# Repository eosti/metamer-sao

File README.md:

# Metamer SAO
A collection of files related to the [Metamer SAO](https://reidsoxharris.me/metamer-sao)

v2 of the badge (first seen at Hackaday 2024) can be found in the `v2_altium` directory, though it's just boardfiles and schematic PDFs. 
Because reasons I had to port it into KiCAD for v2.1, which can be found in the `v2.1_kicad` directory along with all generated gerbers and PnP files required for assembly. 
The `generators` directory has some code for auto-generating C data structures for normalizing brightness. 

Some MicroPython code that you can run on the badge is found in the `micropython` directory. 
The code used on the PY32F002B MCU used to bootstrap I2C is in the `py32` directory, and current builds are in `py32/releases`.

The code I used to generate the graphs for my talk, [Beyond RGB](https://reidsoxharris.me/beyondrgb/) can be found in `python_graphs`.

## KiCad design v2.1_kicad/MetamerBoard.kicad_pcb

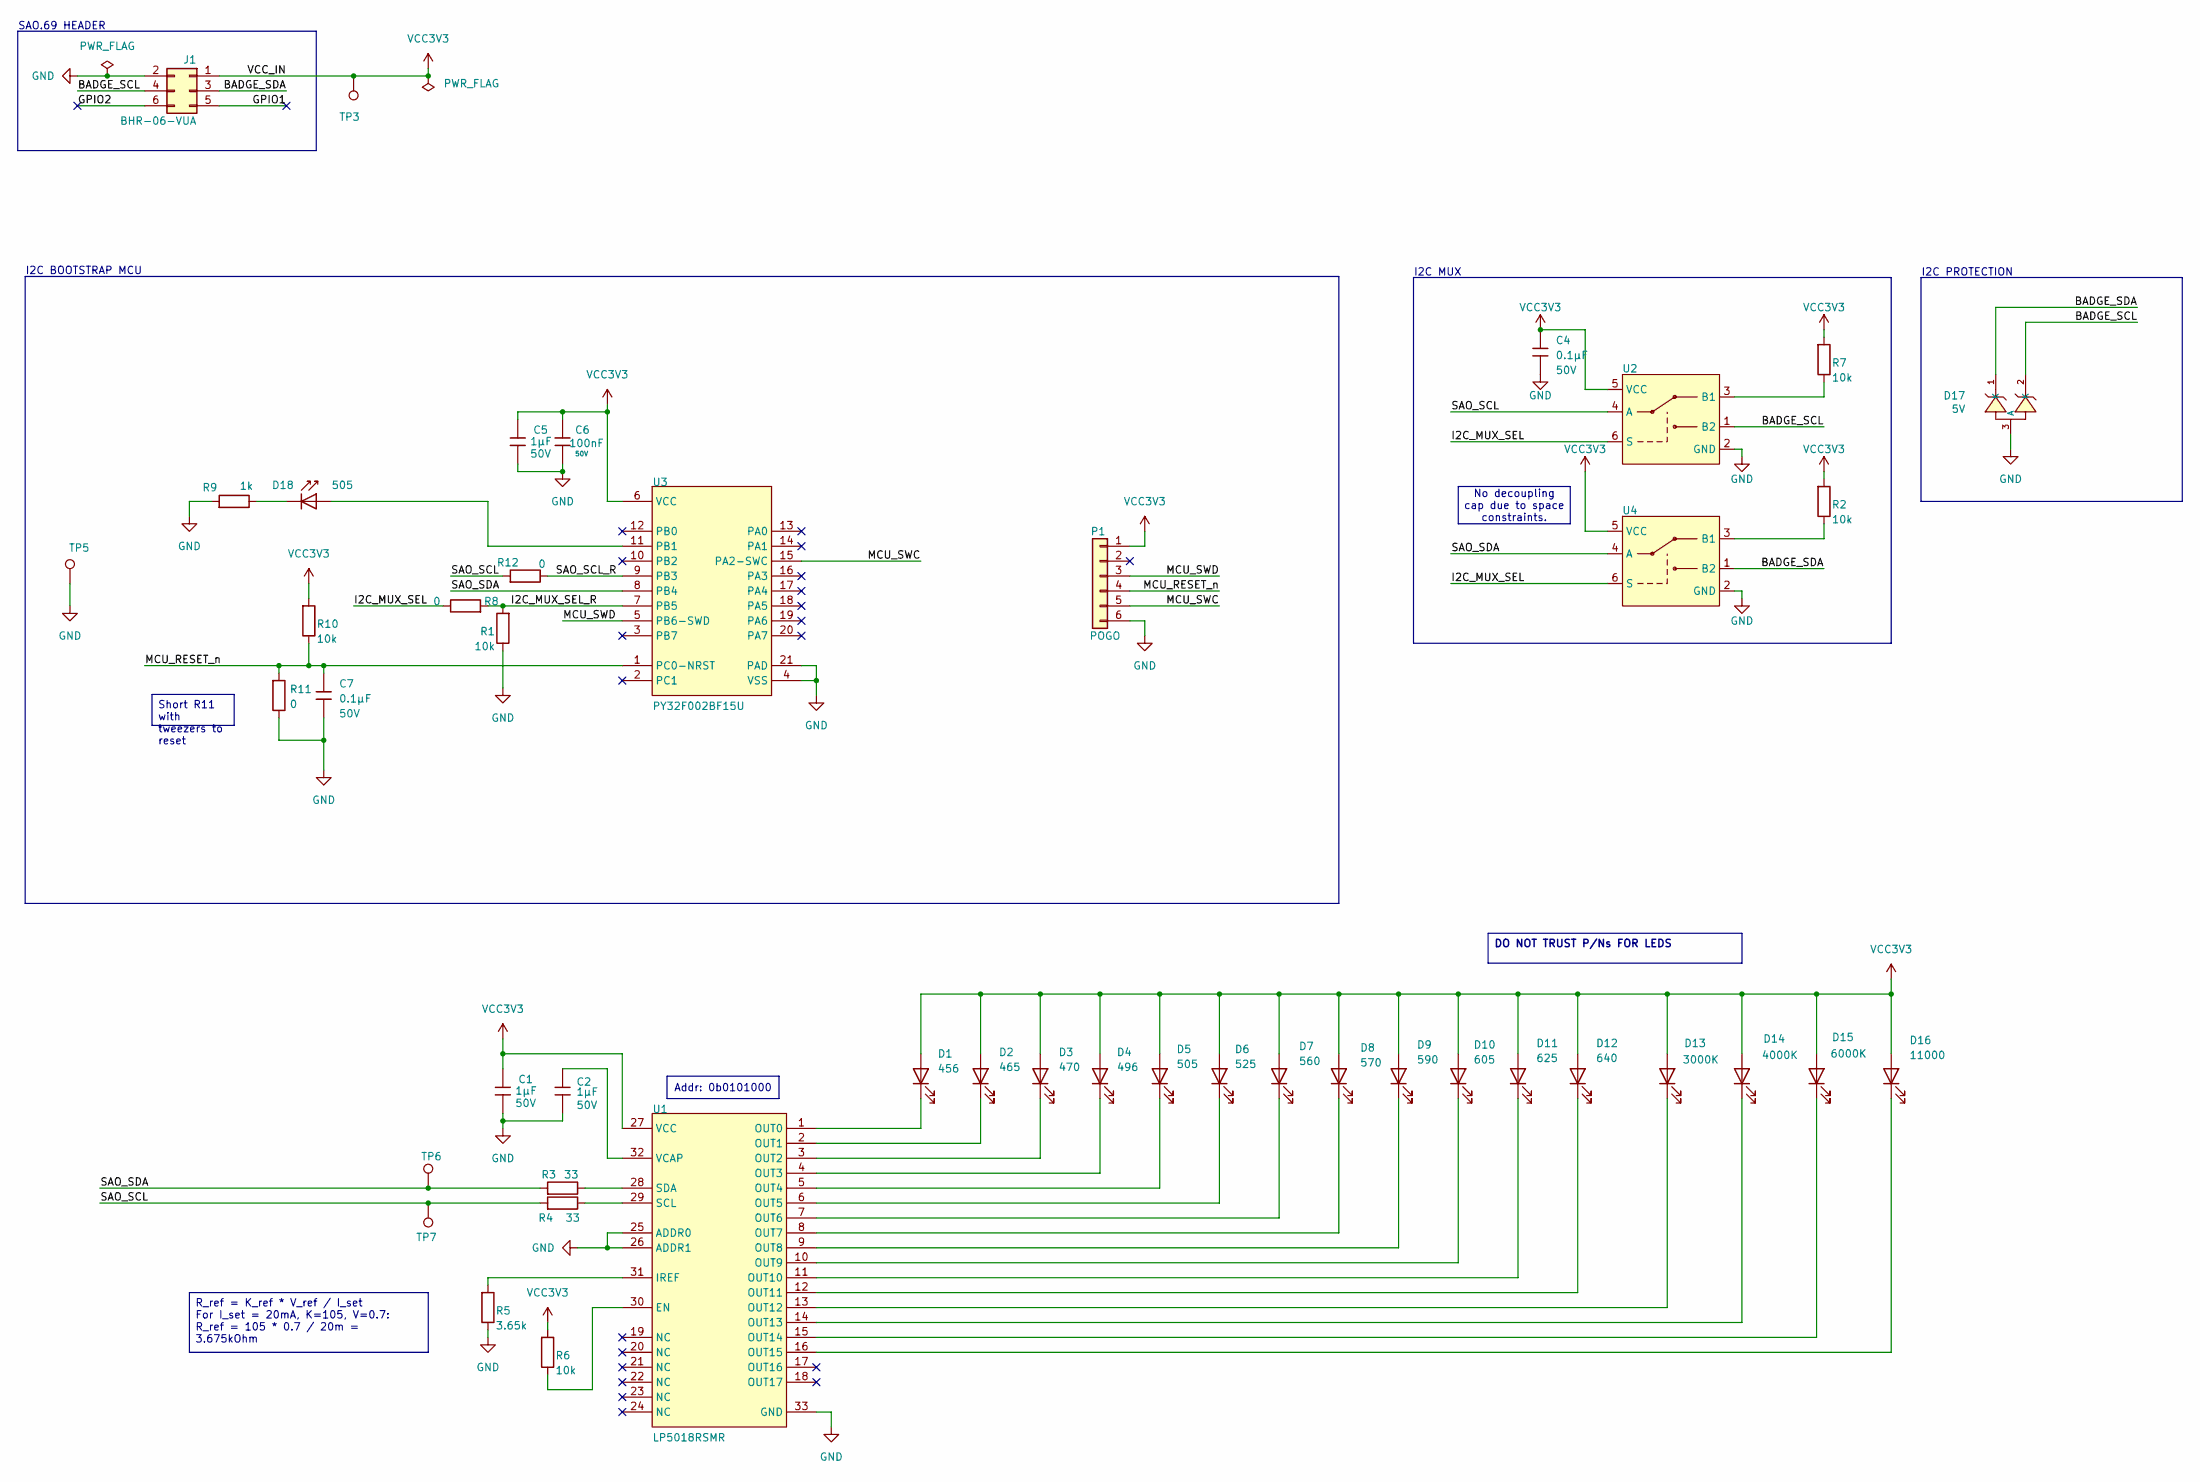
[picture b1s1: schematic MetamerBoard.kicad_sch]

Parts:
C1, C2, C5: CGA3E1X7R1C105M080AC; C_0603; TOLERANCE ±20%; RATINGS AEC-Q200; Part CL10B102KB8NNNC; LCSC C1588
C4, C7: CGA3E2X7R1H104K080AE; C_0603; TOLERANCE ±10%; VOLTAGE - RATED 50V; Part CC0603KRX7R9BB104; LCSC C14663
C6: C_0402; TOLERANCE ±20%; RATINGS AEC-Q200; Part CL05B104KB54PNC; LCSC C307331
D1, D2, D3: QBLP631-IB; LED_0805_2012Metric_Pad1.15x1.40mm_HandSolder_SmallSilk; MANUFACTURER_PART_NUMBER QBLP631-S3
D4, D5: QBLP631-IB; LED_0603_1608Metric_Pad1.05x0.95mm_HandSolder_SmallSilk; MANUFACTURER_PART_NUMBER QBLP631-S3
D6: QBLP631-IG; LED_0805_2012Metric_Pad1.15x1.40mm_HandSolder_SmallSilk; MANUFACTURER_PART_NUMBER QBLP631-S3
D7: LED_0805_2012Metric_Pad1.15x1.40mm_HandSolder_SmallSilk; MANUFACTURER_PART_NUMBER QBLP631-S3
D8: QBLP631-AG; LED_0805_2012Metric_Pad1.15x1.40mm_HandSolder_SmallSilk; MANUFACTURER_PART_NUMBER QBLP631-S3
D9: QBLP631-Y; LED_0805_2012Metric_Pad1.15x1.40mm_HandSolder_SmallSilk; MANUFACTURER_PART_NUMBER QBLP631-S3
D10: QBLP631-O; LED_0805_2012Metric_Pad1.15x1.40mm_HandSolder_SmallSilk
D11: QBLP631-R; LED_0805_2012Metric_Pad1.15x1.40mm_HandSolder_SmallSilk
D12: QBLP631-S3; LED_0805_2012Metric_Pad1.15x1.40mm_HandSolder_SmallSilk; MANUFACTURER_PART_NUMBER QBLP631-S3
D13: QBLP675-IW-WW; LED_SMD3012
D14: QBLP675-IW-NW; LED_SMD3012
D15: QBLP675-IW-CW; LED_SMD3012
D16: QBLP661-IW5-CW; LED_0805_2012Metric_Pad1.15x1.40mm_HandSolder_SmallSilk
D17: H5VHT2U; SOT-23-3_L2.9-W1.5-P1.90-LS2.6-BR; VOLTAGE - BREAKDOWN MIN 16.5V; VOLTAGE - REVERSE STAND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 5V; Part H5VHT2U; LCSC C20615823
D18: QBLP631-R; LED_0603_1608Metric_Pad1.05x0.95mm_HandSolder_SmallSilk; Part KT-0603R; LCSC C2286
J1: BHR-06-VUA; PinHeader_2x03_P2.54mm_Vertical; MANUFACTURER_PART_NUMBER BHR-06-VUA
P1: POGO; 6_Pin_POGO
R1, R2, R6, R7, R10: CRCW060310K0FKEC; R_0603; RATINGS AEC-Q200; TOLERANCE ±1%; Part 0603WAF1002T5E; LCSC C25804
R3, R4: CRCW060333R0FKEA; R_0603; RATINGS AEC-Q200; TOLERANCE ±1%; Part 0603WAF330JT5E; LCSC C23140
R5: CRCW06033K65FKEA; R_0603; TOLERANCE ±1%; RATINGS AEC-Q200; Part 0603WAF3601T5E; LCSC C22980
R8, R11, R12: ERJ-3GEY0R00V; R_0603; RATINGS AEC-Q200; TOLERANCE Jumper; Part 0603WAF0000T5E; LCSC C21189
R9: ERJ-3EKF1001V; R_0603; RATINGS AEC-Q200; TOLERANCE ±1%; Part 0603WAF1001T5E; LCSC C21190
TP3, TP6, TP7: TPAD10R; TestPoint_Pad_D1.0mm
TP5: 5019; TestPoint_Keystone_5019_Miniature
U1: LP5018RSMR; VQFN-32-1EP_4x4mm_P0.4mm_EP2.8x2.8mm; OUTPUT VOLTAGE 5.5V; MANUFACTURER PART NUMBER LP5018RSMR; DIGIKEY DESCRIPTION LED DRIVER
U2, U4: SOT-363_SC-70-6
U3: PY32F002BF15U; QFN-20-1EP_3x3mm_P0.4mm_EP1.65x1.65mm

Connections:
/BADGE_SCL: D17.2 (K), J1.4, U2.1 (B2)
/BADGE_SDA: D17.1 (K), J1.3, U4.1 (B2)
/GPIO1: J1.5
/GPIO2: J1.6
/I2C_MUX_SEL: R8.2, U2.6 (S), U4.6 (S)
/I2C_MUX_SEL_R: R1.1, R8.1, U3.7 (PB5)
/MCU_RESET_n: C7.1, P1.4, R10.2, R11.1, U3.1 (PC0-NRST)
/MCU_SWC: P1.5, U3.15 (PA2-SWC)
/MCU_SWD: P1.3, U3.5 (PB6-SWD)
/SAO_SCL: R4.1, R12.1, TP7.1, U2.4 (A)
/SAO_SCL_R: R12.2, U3.9 (PB3)
/SAO_SDA: R3.1, TP6.1, U3.8 (PB4), U4.4 (A)
GND: C1.2, C2.2, C4.2, C5.2, C6.2, C7.2, D17.3 (A), J1.2, P1.6, R1.2, R5.2, R9.1, R11.2, TP5.1, U1.25 (ADDR0), U1.26 (ADDR1), U1.33 (GND), U2.2 (GND), U3.4 (VSS), U3.21 (PAD), U4.2 (GND)
unnamed: D1.1 (K), U1.1 (OUT0)
unnamed: D2.1 (K), U1.2 (OUT1)
unnamed: D3.1 (K), U1.3 (OUT2)
unnamed: D4.1 (K), U1.4 (OUT3)
unnamed: D5.1 (K), U1.5 (OUT4)
unnamed: D6.1 (K), U1.6 (OUT5)
unnamed: D7.1 (K), U1.7 (OUT6)
unnamed: D8.1 (K), U1.8 (OUT7)
unnamed: D9.1 (K), U1.9 (OUT8)
unnamed: D10.1 (K), U1.10 (OUT9)
unnamed: D11.1 (K), U1.11 (OUT10)
unnamed: D12.1 (K), U1.12 (OUT11)
unnamed: D13.1 (K), U1.13 (OUT12)
unnamed: D14.1 (K), U1.14 (OUT13)
unnamed: D15.1 (K), U1.15 (OUT14)
unnamed: D16.1 (K), U1.16 (OUT15)
unnamed: D18.1, R9.2
unnamed: R6.2, U1.30 (EN)
unnamed: R5.1, U1.31 (IREF)
unnamed: R4.2, U1.29 (SCL)
unnamed: R3.2, U1.28 (SDA)
unnamed: C2.1, U1.32 (VCAP)
unnamed: R7.2, U2.3 (B1)
unnamed: D18.2, U3.11 (PB1)
unnamed: R2.2, U4.3 (B1)
VCC3V3: C1.1, C4.1, C5.1, C6.1, D1.2 (A), D2.2 (A), D3.2 (A), D4.2 (A), D5.2 (A), D6.2 (A), D7.2 (A), D8.2 (A), D9.2 (A), D10.2 (A), D11.2 (A), D12.2 (A), D13.2 (A), D14.2 (A), D15.2 (A), D16.2 (A), J1.1, P1.1, R2.1, R6.1, R7.1, R10.1, TP3.1, U1.27 (VCC), U2.5 (VCC), U3.6 (VCC), U4.5 (VCC)

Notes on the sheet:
SAO.69 HEADER
I2C BOOTSTRAP MCU
I2C MUX
I2C PROTECTION
DO NOT TRUST P/Ns FOR LEDS
Short R11 with tweezers to reset
R_ref = K_ref * V_ref / I_set For I_set = 20mA, K=105, V=0.7: R_ref = 105 * 0.7 / 20m = 3.675kOhm
Addr: 0b0101000
No decoupling cap due to space constraints.

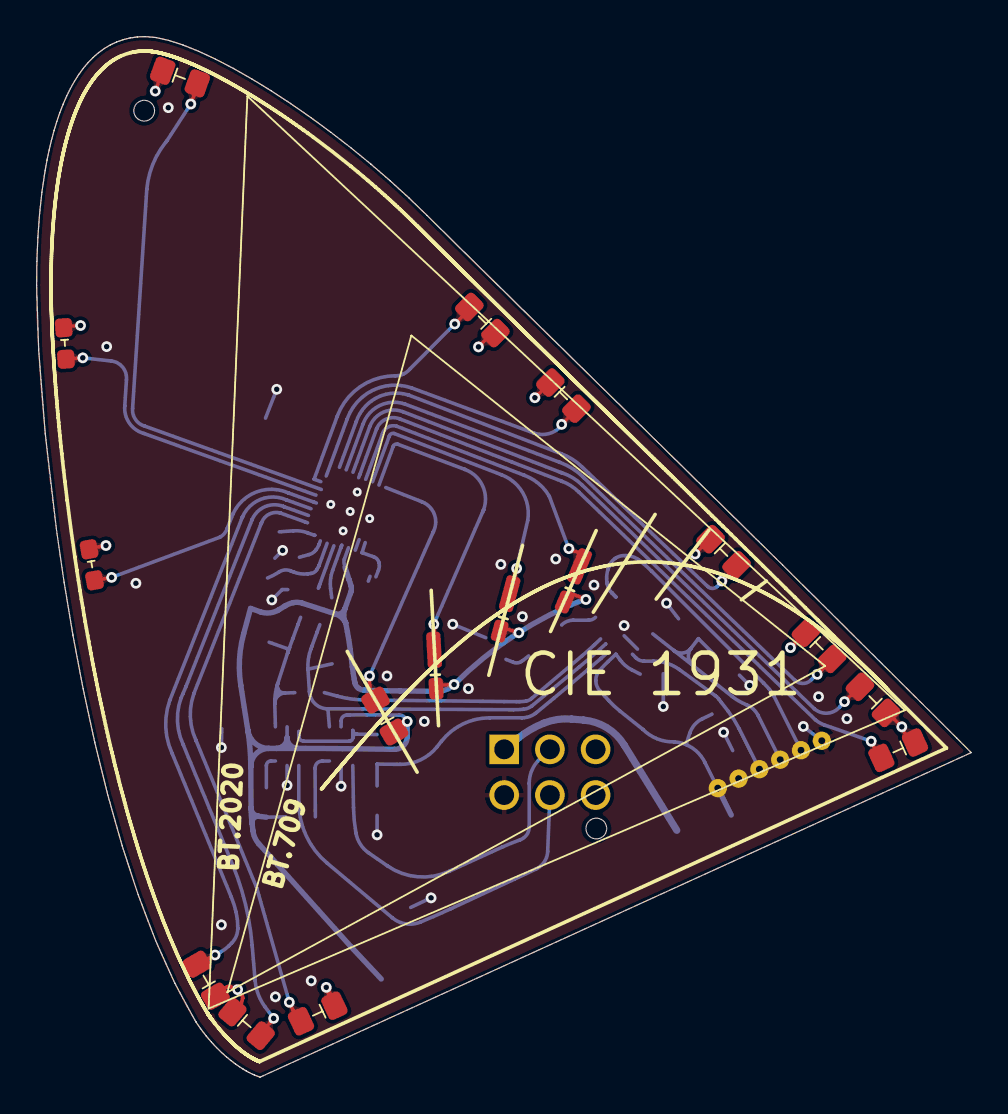
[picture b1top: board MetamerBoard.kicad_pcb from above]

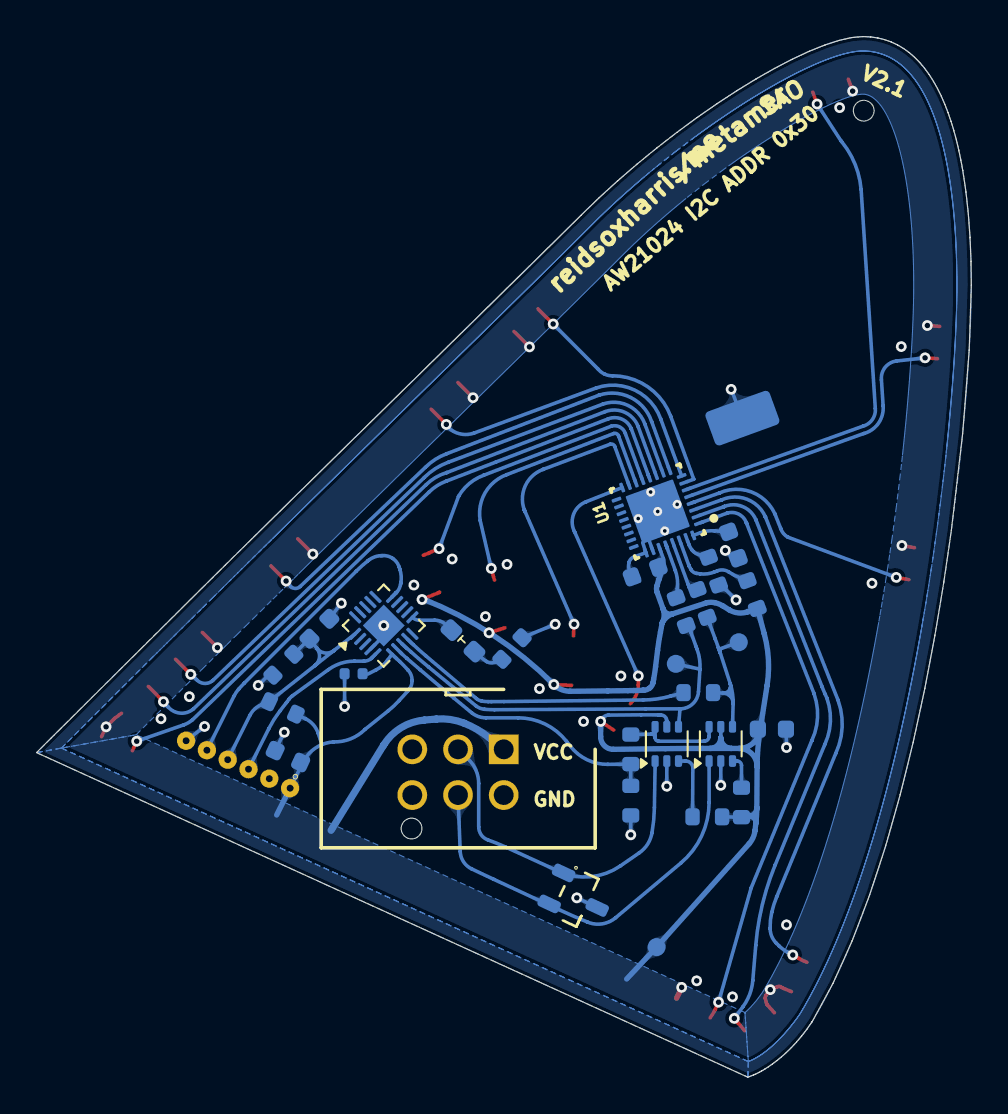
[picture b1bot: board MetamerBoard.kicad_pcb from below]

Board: 2 copper layers, 51.9 x 57.8 mm, 46 parts (30 on the bottom side), 37 nets.

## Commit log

2024-10-31 working code
2024-11-01 update generators
2024-11-01 add py32 code
2024-11-02 fix i2c address aliasing
2024-11-02 add micropico
2024-11-02 clean up build folder, release v1
2024-11-02 add warning about multi-master
2025-10-28 add v2.1 files
2025-10-31 add directory-specific gitignores
2025-10-31 bump PY32 source code for v2.1
2025-10-31 release v2 of firmware
2025-10-31 remove unwanted temporary files
2025-10-31 remove gitmodules
2025-10-31 fix submodules
2026-01-06 reorganize directories
